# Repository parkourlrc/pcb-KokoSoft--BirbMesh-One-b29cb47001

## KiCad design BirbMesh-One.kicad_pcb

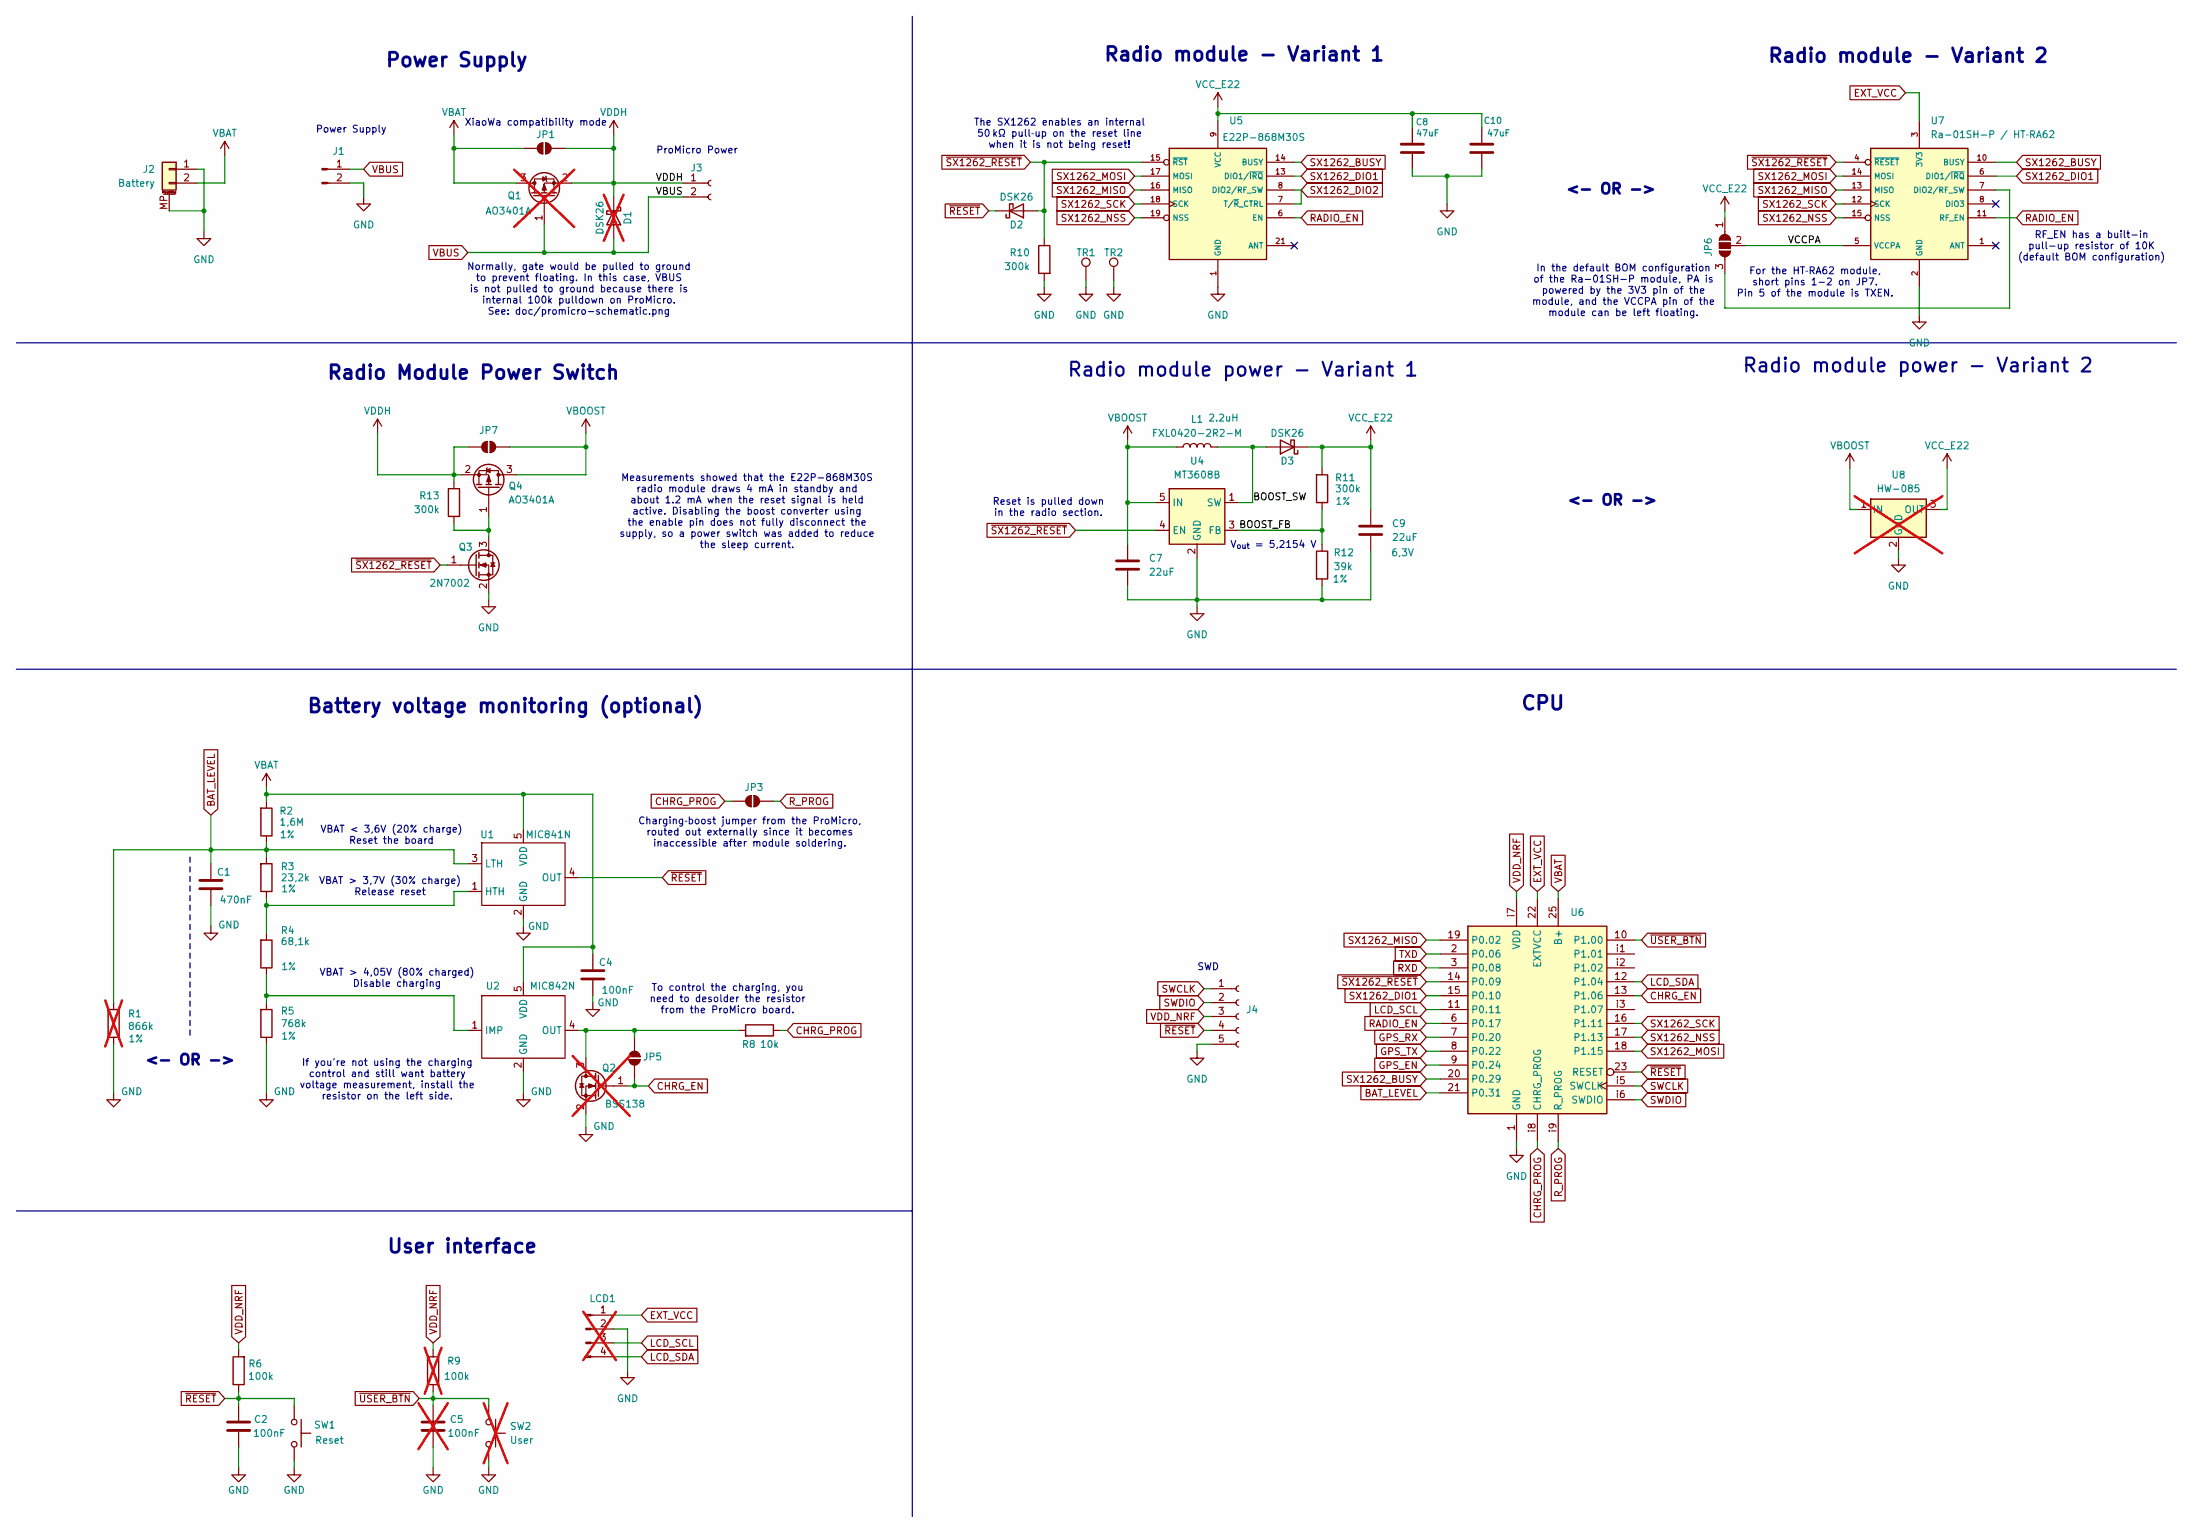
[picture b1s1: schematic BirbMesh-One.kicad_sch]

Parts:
C1: 470nF; C_0603_1608Metric_Pad1.08x0.95mm_HandSolder; Voltage 6,3V
C2: 100nF; C_0603_1608Metric_Pad1.08x0.95mm_HandSolder
C4: 100nF; C_0603_1608Metric_Pad1.08x0.95mm_HandSolder; Voltage 6,3V
C5: 100nF; C_0603_1608Metric_Pad1.08x0.95mm_HandSolder; not fitted
C7: 22uF; C_0603_1608Metric_Pad1.08x0.95mm_HandSolder; MPN CL10A226MQ8NRNC; LCSC C59461
C8, C10: 47uF; C_0805_2012Metric_Pad1.18x1.45mm_HandSolder
C9: 22uF; C_0603_1608Metric_Pad1.08x0.95mm_HandSolder; Voltage 6,3V; MPN CL10A226MQ8NRNC; LCSC C59461
D1: DSK26; D_SOD-123F; LCSC C7502712; not fitted
D2, D3: DSK26; D_SOD-123F; LCSC C7502712
J1: Conn_01x04_Pin; PinHeader_1x02_P2.54mm_Vertical
J2: Battery; JST_PH_S2B-PH-SM4-TB_1x02-1MP_P2.00mm_Horizontal
J3: Conn_01x02_Socket; PinHeader_1x02_P2.54mm_Vertical
J4: Conn_01x05_Socket; PinHeader_1x05_P1.27mm_Vertical
JP1, JP3, JP5: SolderJumper_2_Open; SolderJumper-2_P1.3mm_Open_TrianglePad1.0x1.5mm
JP6: SolderJumper_3_Open; SolderJumper-3_P1.3mm_Open_RoundedPad1.0x1.5mm
JP7: SolderJumper_2_Bridged; SolderJumper-2_P1.3mm_Open_TrianglePad1.0x1.5mm
L1: FXL0420-2R2-M; L_Changjiang_FXL0420; MPN SMMS0650-220M; LCSC C167860
LCD1: Conn_01x04_Pin; PinHeader_1x04_P2.54mm_Vertical; not fitted
Q1: AO3401A; SOT-23; LCSC C15127; not fitted
Q2: BSS138; SOT-23; not fitted
Q3: 2N7002; SOT-23
Q4: AO3401A; SOT-23; LCSC C15127
R1: 866k; R_0603_1608Metric_Pad0.98x0.95mm_HandSolder; Tolerance 1%; not fitted
R2: 1,6M; R_0603_1608Metric_Pad0.98x0.95mm_HandSolder; Tolerance 1%
R3: 23,2k; R_0603_1608Metric_Pad0.98x0.95mm_HandSolder; Tolerance 1%
R4: 68,1k; R_0603_1608Metric_Pad0.98x0.95mm_HandSolder; Tolerance 1%
R5: 768k; R_0603_1608Metric_Pad0.98x0.95mm_HandSolder; Tolerance 1%
R6: 100k; R_0603_1608Metric_Pad0.98x0.95mm_HandSolder
R8: 10k; R_0603_1608Metric_Pad0.98x0.95mm_HandSolder
R9: 100k; R_0603_1608Metric_Pad0.98x0.95mm_HandSolder; not fitted
R10, R13: 300k; R_0603_1608Metric_Pad0.98x0.95mm_HandSolder; MPN 0603WAF1502T5E
R11: 300k; R_0603_1608Metric_Pad0.98x0.95mm_HandSolder; Tolerance 1%
R12: 39k; R_0603_1608Metric_Pad0.98x0.95mm_HandSolder; Tolerance 1%; LCSC C22843
SW1: Reset; SW_Push_SPST_NO_Alps_SKRK
SW2: User; SW_Push_SPST_NO_Alps_SKRK; not fitted
TR1, TR2: PTH; PinSocket_1x01_P2.54mm_Vertical
U1: MIC841N; SOT-353_SC-70-5
U2: MIC842N; SOT-353_SC-70-5
U4: MT3608B; SOT-23-6; LCSC C2932326
U5: E22P-868M30S
U6: ProMicro-all-pins_smd
U7: Ra-01SH-P / HT‑RA62; Ra-01SH-P
U8: HW-085; not fitted

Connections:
/BOOST_FB: R11.1, R12.1, U4.3 (FB)
/BOOST_SW: D3.2 (A), L1.2, U4.1 (SW)
/VCCPA: JP6.2 (C), U7.5 (VCCPA)
BAT_LEVEL: C1.1, R1.2, R2.1, R3.2, U1.3 (LTH), U6.21 (P0.31)
CHRG_EN: JP5.1 (A), Q2.1 (G), U6.13 (P1.06)
CHRG_PROG: JP3.1 (A), R8.1, U6.i8 (CHRG_PROG)
EXT_VCC: LCD1.1, U6.22 (EXTVCC), U7.3 (3V3)
GND: C1.2, C2.1, C4.2, C5.1, C7.2, C8.1, C9.2, C10.1, J1.2, J2.1, J2.MP (MountPin), J4.5, LCD1.2, Q2.2 (S), Q3.2 (S), R1.1, R5.1, R10.2, R12.2, SW1.1, SW2.2, TR1.1, TR2.1, U1.2 (GND), U2.2 (GND), U4.2 (GND), U5.1 (GND), U6.1 (GND), U7.2 (GND), U8.2 (GND)
GPS_EN: U6.9 (P0.24)
GPS_RX: U6.7 (P0.20)
GPS_TX: U6.8 (P0.22)
LCD_SCL: LCD1.3, U6.11 (P0.11)
LCD_SDA: LCD1.4, U6.12 (P1.04)
unnamed: JP5.2 (B), Q2.3 (D), R8.2, U2.4 (OUT)
unnamed: JP6.3 (B), U7.7 (DIO2/RF_SW)
unnamed: Q3.3 (D), Q4.1 (G), R13.2
unnamed: R3.1, R4.2, U1.1 (HTH)
unnamed: R4.1, R5.2, U2.1 (IMP)
RADIO_EN: U5.6 (EN), U6.6 (P0.17), U7.11 (RF_EN)
RXD: U6.3 (P0.08)
R_PROG: JP3.2 (B), U6.i9 (R_PROG)
SWCLK: J4.1, U6.i5 (SWCLK)
SWDIO: J4.2, U6.i6 (SWDIO)
SX1262_BUSY: U5.14 (BUSY), U6.20 (P0.29), U7.10 (BUSY)
SX1262_DIO1: U5.13 (DIO1/~IRQ), U6.15 (P0.10), U7.6 (DIO1/~IRQ)
SX1262_DIO2: U5.7 (T/~R_CTRL), U5.8 (DIO2/RF_SW)
SX1262_MISO: U5.16 (MISO), U6.19 (P0.02), U7.13 (MISO)
SX1262_MOSI: U5.17 (MOSI), U6.18 (P1.15), U7.14 (MOSI)
SX1262_NSS: U5.19 (NSS), U6.17 (P1.13), U7.15 (NSS)
SX1262_SCK: U5.18 (SCK), U6.16 (P1.11), U7.12 (SCK)
TXD: U6.2 (P0.06)
VBAT: C4.1, J2.2, JP1.1 (A), Q1.3 (D), R2.2, U1.5 (VDD), U2.5 (VDD), U6.25 (B+)
VBUS: D1.2 (A), J1.1, J3.2, Q1.1 (G)
VCC_E22: C8.2, C9.1, C10.2, D3.1 (K), JP6.1 (A), R11.2, U5.9 (VCC), U8.3 (OUT)
VDD_NRF: J4.3, R6.2, R9.2, U6.i7 (VDD)
~RESET: C2.2, D2.1 (K), J4.4, R6.1, SW1.2, U1.4 (OUT), U6.23 (RESET)
~SX1262_RESET: D2.2 (A), Q3.1 (G), R10.1, U4.4 (EN), U5.15 (~RST), U6.14 (P0.09), U7.4 (~RESET)
~USER_BTN: C5.2, R9.1, SW2.1, U6.10 (P1.00)

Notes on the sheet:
Radio Module Power Switch
Radio module - Variant 2
For the HT‑RA62 module, short pins 1-2 on JP7. Pin 5 of the module is TXEN.
To control the charging, you need to desolder the resistor from the ProMicro board.
SWD
VBAT > 4,05V (80% charged) Disable charging
Radio module power - Variant 1
Radio module - Variant 1
The SX1262 enables an internal 50 kΩ pull‑up on the reset line when it is not being reset!
<- OR ->
VBAT > 3,7V (30% charge) Release reset
Power Supply
User interface
Battery voltage monitoring (optional)
V_{out} = 5,2154 V
Radio module power - Variant 2
XiaoWa compatibility mode
Normally, gate would be pulled to ground to prevent floating. In this case, VBUS is not pulled to ground because there is internal 100k pulldown on ProMicro. See: doc/promicro-schematic.png
Charging‑boost jumper from the ProMicro, routed out externally since it becomes inaccessible after module soldering.
CPU
Reset is pulled down in the radio section.
ProMicro Power
In the default BOM configuration of the Ra-01SH-P module, PA is powered by the 3V3 pin of the module, and the VCCPA pin of the module can be left floating.
VBAT < 3,6V (20% charge) Reset the board
Measurements showed that the E22P-868M30S radio module draws 4 mA in standby and about 1.2 mA when the reset signal is held active. Disabling the boost converter using the enable pin does not fully disconnect the supply, so a power switch was added to reduce the sleep current.
RF_EN has a built-in pull-up resistor of 10K (default BOM configuration)
If you're not using the charging control and still want battery voltage measurement, install the resistor on the left side.

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
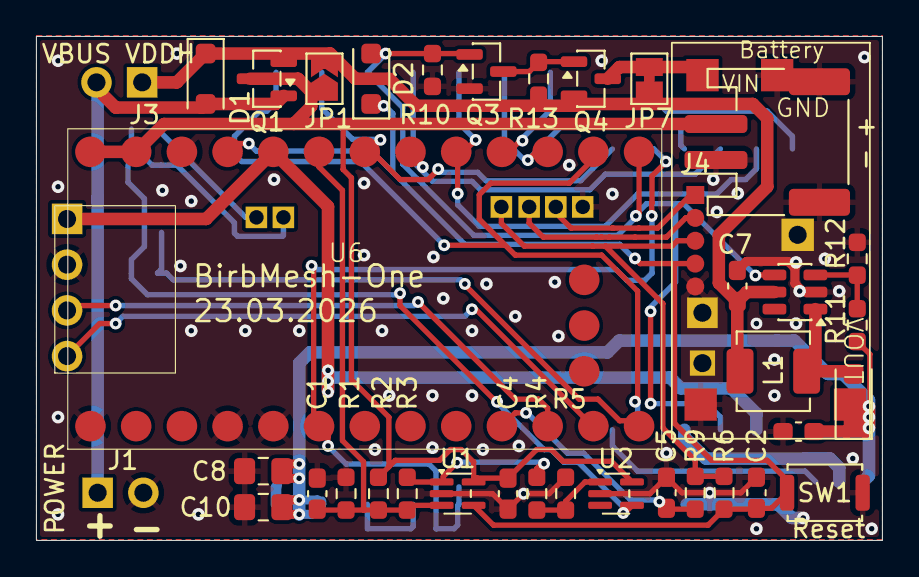
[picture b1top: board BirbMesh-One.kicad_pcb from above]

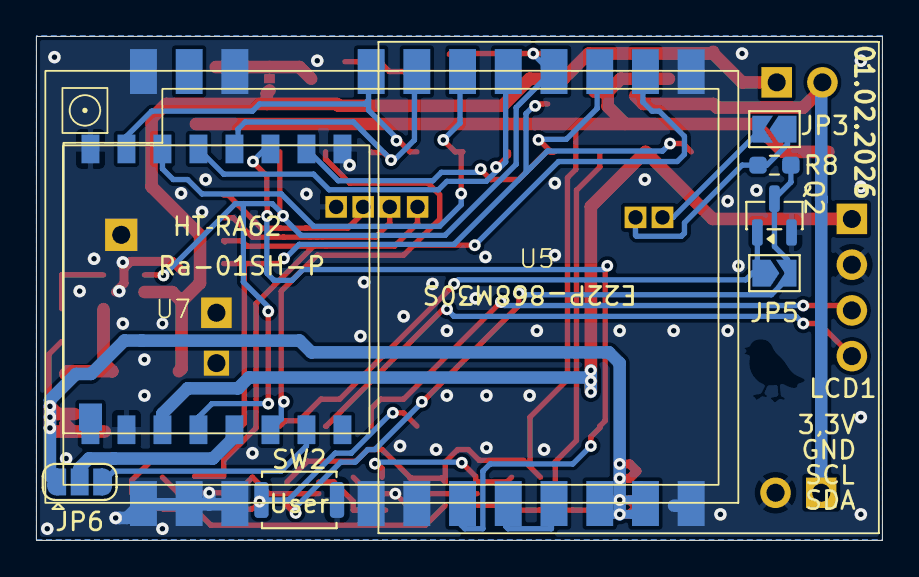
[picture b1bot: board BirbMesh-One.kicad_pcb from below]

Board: 2 copper layers, 47.0 x 28.0 mm, 49 parts (9 on the bottom side), 35 nets.

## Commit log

2026-03-14 symbols: Improve E22 footprint thermal design and silkscreen
    Relocate thermal pads for to correct positions, change GND pad
    connections to solid for better heat dissipation, redraw silkscreen
    markings to improve readability.
2026-03-15 symbols: Update thermal pad connection for Ra-01SH-P
    Improve heat transfer for thermal pad by removing thermal reliefs.
2026-03-15 symbols: Correct pad placement for HW-085 voltage converter
    Adjust footprint layout to match dimensions from PCB AS32 revision V8.1.
2026-03-16 symbols: Adjust ProMicro footprint to account USB connector
    Fix silkscreen and courtyard in ProMicro footprint to account for USB
    connector overhang.
2026-03-19 sch: pcb: Update layout
    Move the battery connector deeper into the board outline so the battry
    plug no longer protrudes beyond the PCB edge. Add pin labels.
    Fix the ordering of the JP6 pins that switch between the Ra-01SH-P and
    HT-RA62 modules. Fix the thermal pad for the Ra-01SH-P module.
    Reorganize the schematic layout to improve readability.
2026-03-19 pcb: Use updated footprints
    Use updated footprints for ProMicro, E22 and HW-085 booster.
2026-03-19 pcb: Reduce board height to fit the enclosure
    Reduce PCB height to fit the enclosure, adjust the radio module position
    and reroute signal traces that previously extended toward the board edge
    for potential cut‑off.
2026-03-19 sch: pcb: Update radio module power routing
    Update the schematic layout and route power for both boost converter
    variants through the power switch.
    Measurements showed that the E22P-868M30S radio module draws 4 mA in
    standby and about 1.2 mA when the reset signal is held active.
    Disabling the boost converter using the enable pin does not fully
    disconnect the supply, so a power switch was added to reduce the sleep
2026-03-19 pcb: Update silkscreen
    Remove unnecessary PinHead graphics and add labels for the radio
    modules.
